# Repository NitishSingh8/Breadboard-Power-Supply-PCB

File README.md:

#  Breadboard Power Supply PCB Design

##  Project Overview
This project focuses on designing a **Breadboard Power Supply Module PCB** that provides a stable and regulated DC output for breadboard-based electronic prototyping.

The PCB is compact and designed to directly interface with a standard breadboard, making it suitable for testing and developing electronic circuits.

---
##  Motivation
Breadboards require a stable and portable power source. 
This project was designed to create a compact and efficient 
solution for powering circuits during prototyping.

##  Objectives
- Design a reliable and compact power supply for breadboard use
- Implement proper PCB layout techniques
- Generate manufacturing-ready files (Gerber, Drill)
- Validate the design using 3D visualization

---

## Tools Used
- **KiCad** (Schematic & PCB Design)
- PCB Viewer (3D Visualization)

---

##  Technical Specifications
- PCB Type: Breadboard Compatible Power Module
- Layers: 2-Layer PCB (Top & Bottom)
- Copper Layers: F.Cu & B.Cu
- Ground Plane: Copper Zone Filled
- Output: Regulated DC Supply
- File Outputs: Gerber Files, Drill Files, Manufacturing Report

---

##  Electrical Design Details
- Input Voltage: 7V–12V DC
- Output Voltage: 5V regulated
- Voltage Regulator Used:  7805 
- Filtering Capacitors: 10uF , 0.1uF
- Resistor: 330 ohm

  ---

  ##  Design Considerations
- Capacitors placed close to the regulator for voltage stability.
- Short traces are used to reduce noise and voltage drop.
- Ground plane implemented for better performance.
- Components arranged for compact breadboard compatibility.

    ---
  
  ##  Working Principle
The input DC voltage is regulated using a linear voltage regulator. 
Capacitors are used for filtering and стабlizing the output voltage. 
The regulated output is provided to breadboard rails for circuit prototyping.

---

##  Design Workflow
1. Schematic Design
2. Footprint Assignment
3. PCB Layout Design
4. Component Placement Optimization
5. Routing (F.Cu & B.Cu Layers)
6. Copper Zone Filling (Ground Plane)
7. 3D Visualization (Front & Back)
8. Gerber File Generation

---

##  Project Files
- `/Schematic` → Circuit design files
- `/PCB Layout` → PCB design files
- `/Gerber` → Manufacturing files
- `/Images` → PCB images (3D, layout, schematic)

---

##  Project Preview

### 🔹Schematic

### 🔹 PCB Layout (Zone Filled)

### 🔹 3D View (Front)

### 🔹 3D View (Back)

### 🔹 Top Layer (F.Cu)

### 🔹 Bottom Layer (B.Cu)

---

##  Bill of Materials (BOM)

| Component | Value | Quantity |
|----------|------|----------|
| Voltage Regulator | 7805 | 1 |
| Capacitor | 10uF | 2 |
| Capacitor | 0.1uF | 2 |
| LED | - | 1 |
| Resistor | 330Ω | 1 |

---

## Applications
- Powering Arduino / microcontroller circuits
- Breadboard prototyping
- Testing analog and digital circuits

  ---
  
##  Key Features
- Compact and breadboard-friendly design
- Clean and optimized PCB routing
- Ground plane for improved stability
- Manufacturing-ready design outputs

---

##  Skills Demonstrated
- PCB Design
- Schematic Capture
- Component Placement
- Routing Techniques
- Design for Manufacturing (DFM)

---

##  Future Improvements
- Add adjustable voltage output
- Include current limiting protection
- Improve efficiency with switching regulators

---

##  Feedback
Feel free to suggest improvements or provide feedback!

---

## Author
**Nitish Singh**  
Electronics & Communication Engineer

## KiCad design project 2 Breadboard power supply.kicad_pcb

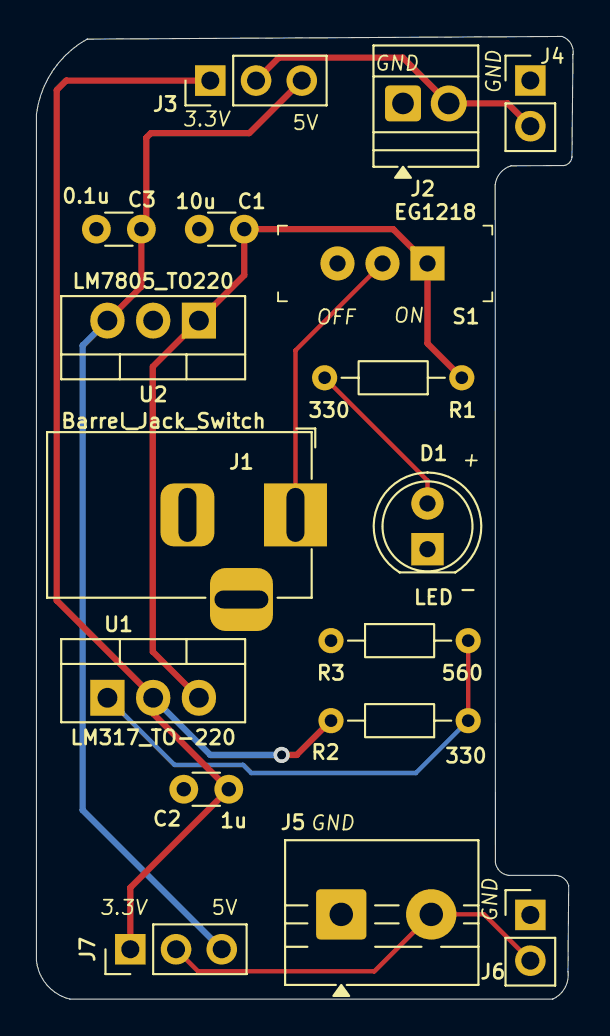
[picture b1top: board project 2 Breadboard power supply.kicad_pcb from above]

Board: 2 copper layers, 29.8 x 53.5 mm, 17 parts (0 on the bottom side), 9 nets.

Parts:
C1: 10u; C_Disc_D3.0mm_W1.6mm_P2.50mm
C2: 1u; C_Disc_D3.0mm_W1.6mm_P2.50mm
C3: 0.1u; C_Disc_D3.0mm_W1.6mm_P2.50mm
D1: LED; LED_D5.0mm
J1: Barrel_Jack_Switch; BarrelJack_Horizontal
J2: Screw_Terminal_01x02; TerminalBlock_Xinya_XY308-2.54-2P_1x02_P2.54mm_Horizontal
J3, J7: Conn_01x03_Pin; PinHeader_1x03_P2.54mm_Vertical
J4, J6: Conn_01x02_Pin; PinHeader_1x02_P2.54mm_Vertical
J5: Screw_Terminal_01x02; TerminalBlock_MaiXu_MX126-5.0-02P_1x02_P5.00mm
R1, R2: 330; R_Axial_DIN0204_L3.6mm_D1.6mm_P7.62mm_Horizontal
R3: 560; R_Axial_DIN0204_L3.6mm_D1.6mm_P7.62mm_Horizontal
S1: EG1218; Switch_Slide_11.6x4mm_EG1218
U1: LM317_TO-220; TO-220-3_Vertical
U2: LM7805_TO220; TO-220-3_Vertical

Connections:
/3.3V: C2.1, J3.1, J7.1, R2.2, U1.2 (VO)
/5V: C3.1, J3.3, J7.3, U2.3 (VO)
/12V: C1.1, R1.1, S1.1, U1.3 (VI), U2.1 (VI)
/PWR_ input: J1.1, S1.2
/PWR_OUT_B0T: J5.2, J6.2, J7.2
/PWR_OUT_TOP: J2.2, J3.2, J4.2
GND: C1.2, C2.2, C3.2, D1.1 (K), J1.2, J1.3, J2.1, J4.1, J5.1, J6.1, R3.1, U2.2 (GND)
unnamed: D1.2 (A), R1.2
unnamed: R2.1, R3.2, U1.1 (ADJ)
